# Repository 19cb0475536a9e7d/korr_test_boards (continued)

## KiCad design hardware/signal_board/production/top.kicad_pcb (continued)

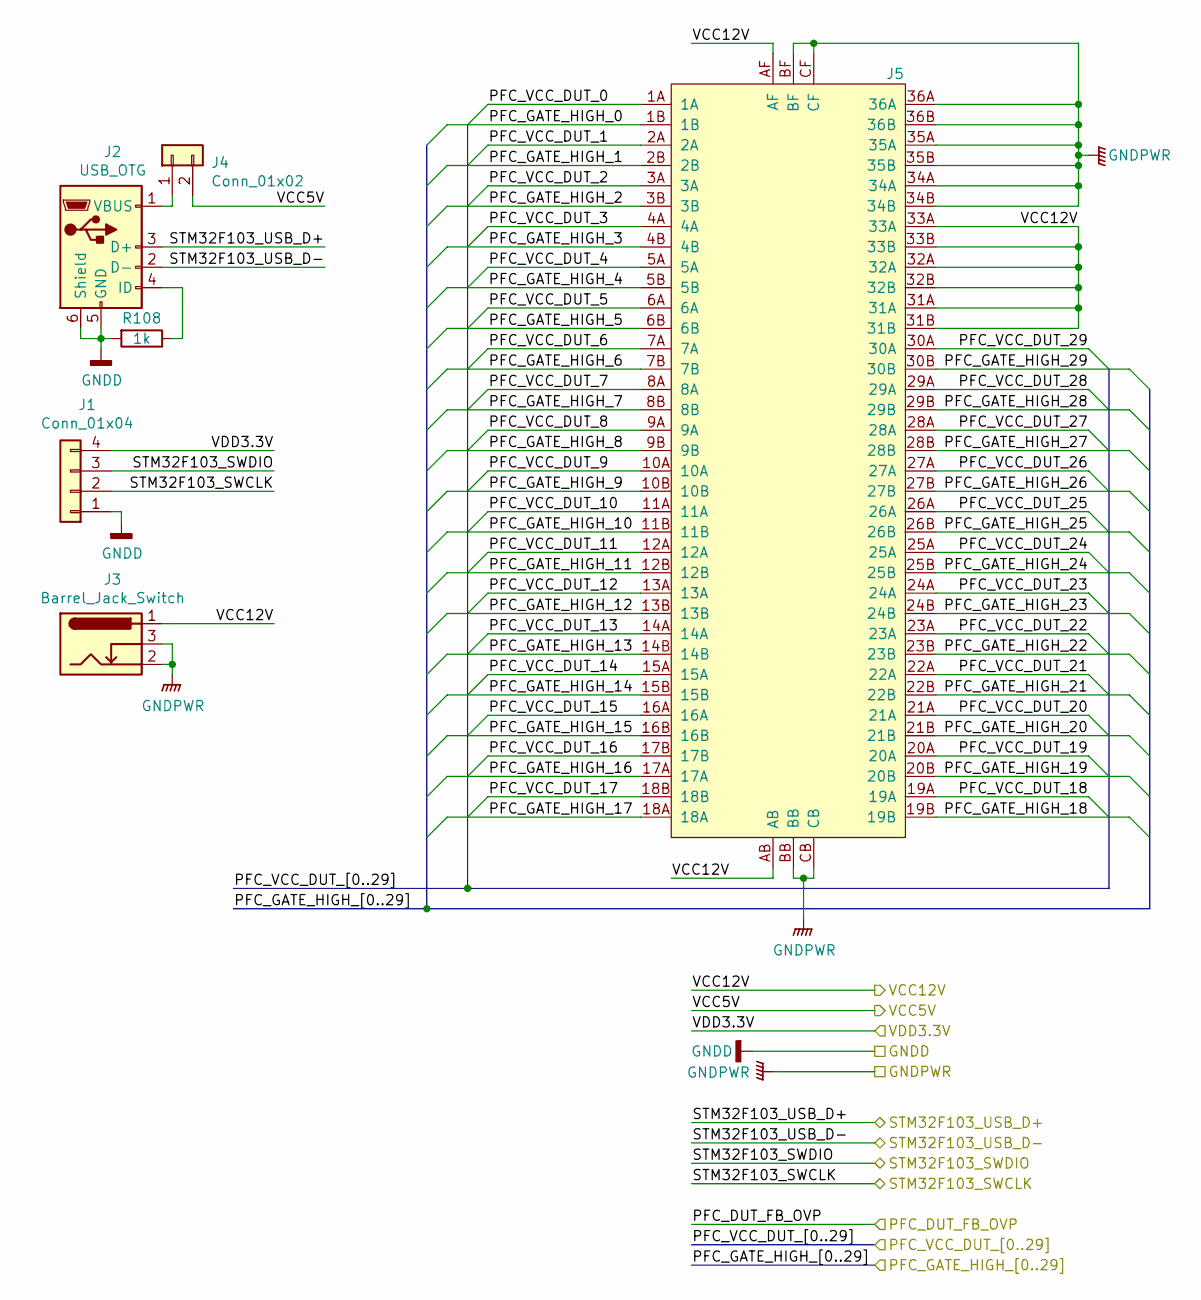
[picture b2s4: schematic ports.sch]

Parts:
J1: Conn_01x04; PinHeader_1x04_P2.54mm_Vertical
J2: USB_OTG; USB_Micro-B_GCT_USB3076-30-A
J3: Barrel_Jack_Switch; BarrelJack_Horizontal
J4: Conn_01x02; PinHeader_1x02_P2.54mm_Vertical
J5: panel_pin; panel_pin_small
R108: 1k; R_0603_1608Metric

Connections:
/PFC_GATE_HIGH_0: J5.1B; also elsewhere on the board
/PFC_GATE_HIGH_1: J5.2B; also elsewhere on the board
/PFC_GATE_HIGH_2: J5.3B; also elsewhere on the board
/PFC_GATE_HIGH_3: J5.4B; also elsewhere on the board
/PFC_GATE_HIGH_4: J5.5B; also elsewhere on the board
/PFC_GATE_HIGH_5: J5.6B; also elsewhere on the board
/PFC_GATE_HIGH_6: J5.7B; also elsewhere on the board
/PFC_GATE_HIGH_7: J5.8B; also elsewhere on the board
/PFC_GATE_HIGH_8: J5.9B; also elsewhere on the board
/PFC_GATE_HIGH_9: J5.10B; also elsewhere on the board
/PFC_GATE_HIGH_10: J5.11B; also elsewhere on the board
/PFC_GATE_HIGH_11: J5.12B; also elsewhere on the board
/PFC_GATE_HIGH_12: J5.13B; also elsewhere on the board
/PFC_GATE_HIGH_13: J5.14B; also elsewhere on the board
/PFC_GATE_HIGH_14: J5.15B; also elsewhere on the board
/PFC_GATE_HIGH_15: J5.16B; also elsewhere on the board
/PFC_GATE_HIGH_16: J5.17A; also elsewhere on the board
/PFC_GATE_HIGH_17: J5.18A; also elsewhere on the board
/PFC_GATE_HIGH_18: J5.19B; also elsewhere on the board
/PFC_GATE_HIGH_19: J5.20B; also elsewhere on the board
/PFC_GATE_HIGH_20: J5.21B; also elsewhere on the board
/PFC_GATE_HIGH_21: J5.22B; also elsewhere on the board
/PFC_GATE_HIGH_22: J5.23B; also elsewhere on the board
/PFC_GATE_HIGH_23: J5.24B; also elsewhere on the board
/PFC_GATE_HIGH_24: J5.25B; also elsewhere on the board
/PFC_GATE_HIGH_25: J5.26B; also elsewhere on the board
/PFC_GATE_HIGH_26: J5.27B; also elsewhere on the board
/PFC_GATE_HIGH_27: J5.28B; also elsewhere on the board
/PFC_GATE_HIGH_28: J5.29B; also elsewhere on the board
/PFC_GATE_HIGH_29: J5.30B; also elsewhere on the board
/PFC_VCC_DUT_0: J5.1A; also elsewhere on the board
/PFC_VCC_DUT_1: J5.2A; also elsewhere on the board
/PFC_VCC_DUT_2: J5.3A; also elsewhere on the board
/PFC_VCC_DUT_3: J5.4A; also elsewhere on the board
/PFC_VCC_DUT_4: J5.5A; also elsewhere on the board
/PFC_VCC_DUT_5: J5.6A; also elsewhere on the board
/PFC_VCC_DUT_6: J5.7A; also elsewhere on the board
/PFC_VCC_DUT_7: J5.8A; also elsewhere on the board
/PFC_VCC_DUT_8: J5.9A; also elsewhere on the board
/PFC_VCC_DUT_9: J5.10A; also elsewhere on the board
/PFC_VCC_DUT_10: J5.11A; also elsewhere on the board
/PFC_VCC_DUT_11: J5.12A; also elsewhere on the board
/PFC_VCC_DUT_12: J5.13A; also elsewhere on the board
/PFC_VCC_DUT_13: J5.14A; also elsewhere on the board
/PFC_VCC_DUT_14: J5.15A; also elsewhere on the board
/PFC_VCC_DUT_15: J5.16A; also elsewhere on the board
/PFC_VCC_DUT_16: J5.17B; also elsewhere on the board
/PFC_VCC_DUT_17: J5.18B; also elsewhere on the board
/PFC_VCC_DUT_18: J5.19A; also elsewhere on the board
/PFC_VCC_DUT_19: J5.20A; also elsewhere on the board
/PFC_VCC_DUT_20: J5.21A; also elsewhere on the board
/PFC_VCC_DUT_21: J5.22A; also elsewhere on the board
/PFC_VCC_DUT_22: J5.23A; also elsewhere on the board
/PFC_VCC_DUT_23: J5.24A; also elsewhere on the board
/PFC_VCC_DUT_24: J5.25A; also elsewhere on the board
/PFC_VCC_DUT_25: J5.26A; also elsewhere on the board
/PFC_VCC_DUT_26: J5.27A; also elsewhere on the board
/PFC_VCC_DUT_27: J5.28A; also elsewhere on the board
/PFC_VCC_DUT_28: J5.29A; also elsewhere on the board
/PFC_VCC_DUT_29: J5.30A; also elsewhere on the board
/STM32F103_SWCLK: J1.2; also elsewhere on the board
/STM32F103_SWDIO: J1.3; also elsewhere on the board
/STM32F103_USB_D+: J2.3 (D+); also elsewhere on the board
/STM32F103_USB_D-: J2.2 (D-); also elsewhere on the board
/VCC5V: J4.2; also elsewhere on the board
/VCC12V: J3.1, J5.31A, J5.31B, J5.32A, J5.32B, J5.33A, J5.33B, J5.AB, J5.AF; also elsewhere on the board
/VDD3.3V: J1.4; also elsewhere on the board
GNDA: J1.1, J2.5 (GND), J2.6 (Shield), J3.2, J3.3, J5.34A, J5.34B, J5.35A, J5.35B, J5.36A, J5.36B, J5.BB, J5.BF, J5.CB, J5.CF, R108.2; also elsewhere on the board
unnamed: J2.1 (VBUS), J4.1
unnamed: J2.4 (ID), R108.1

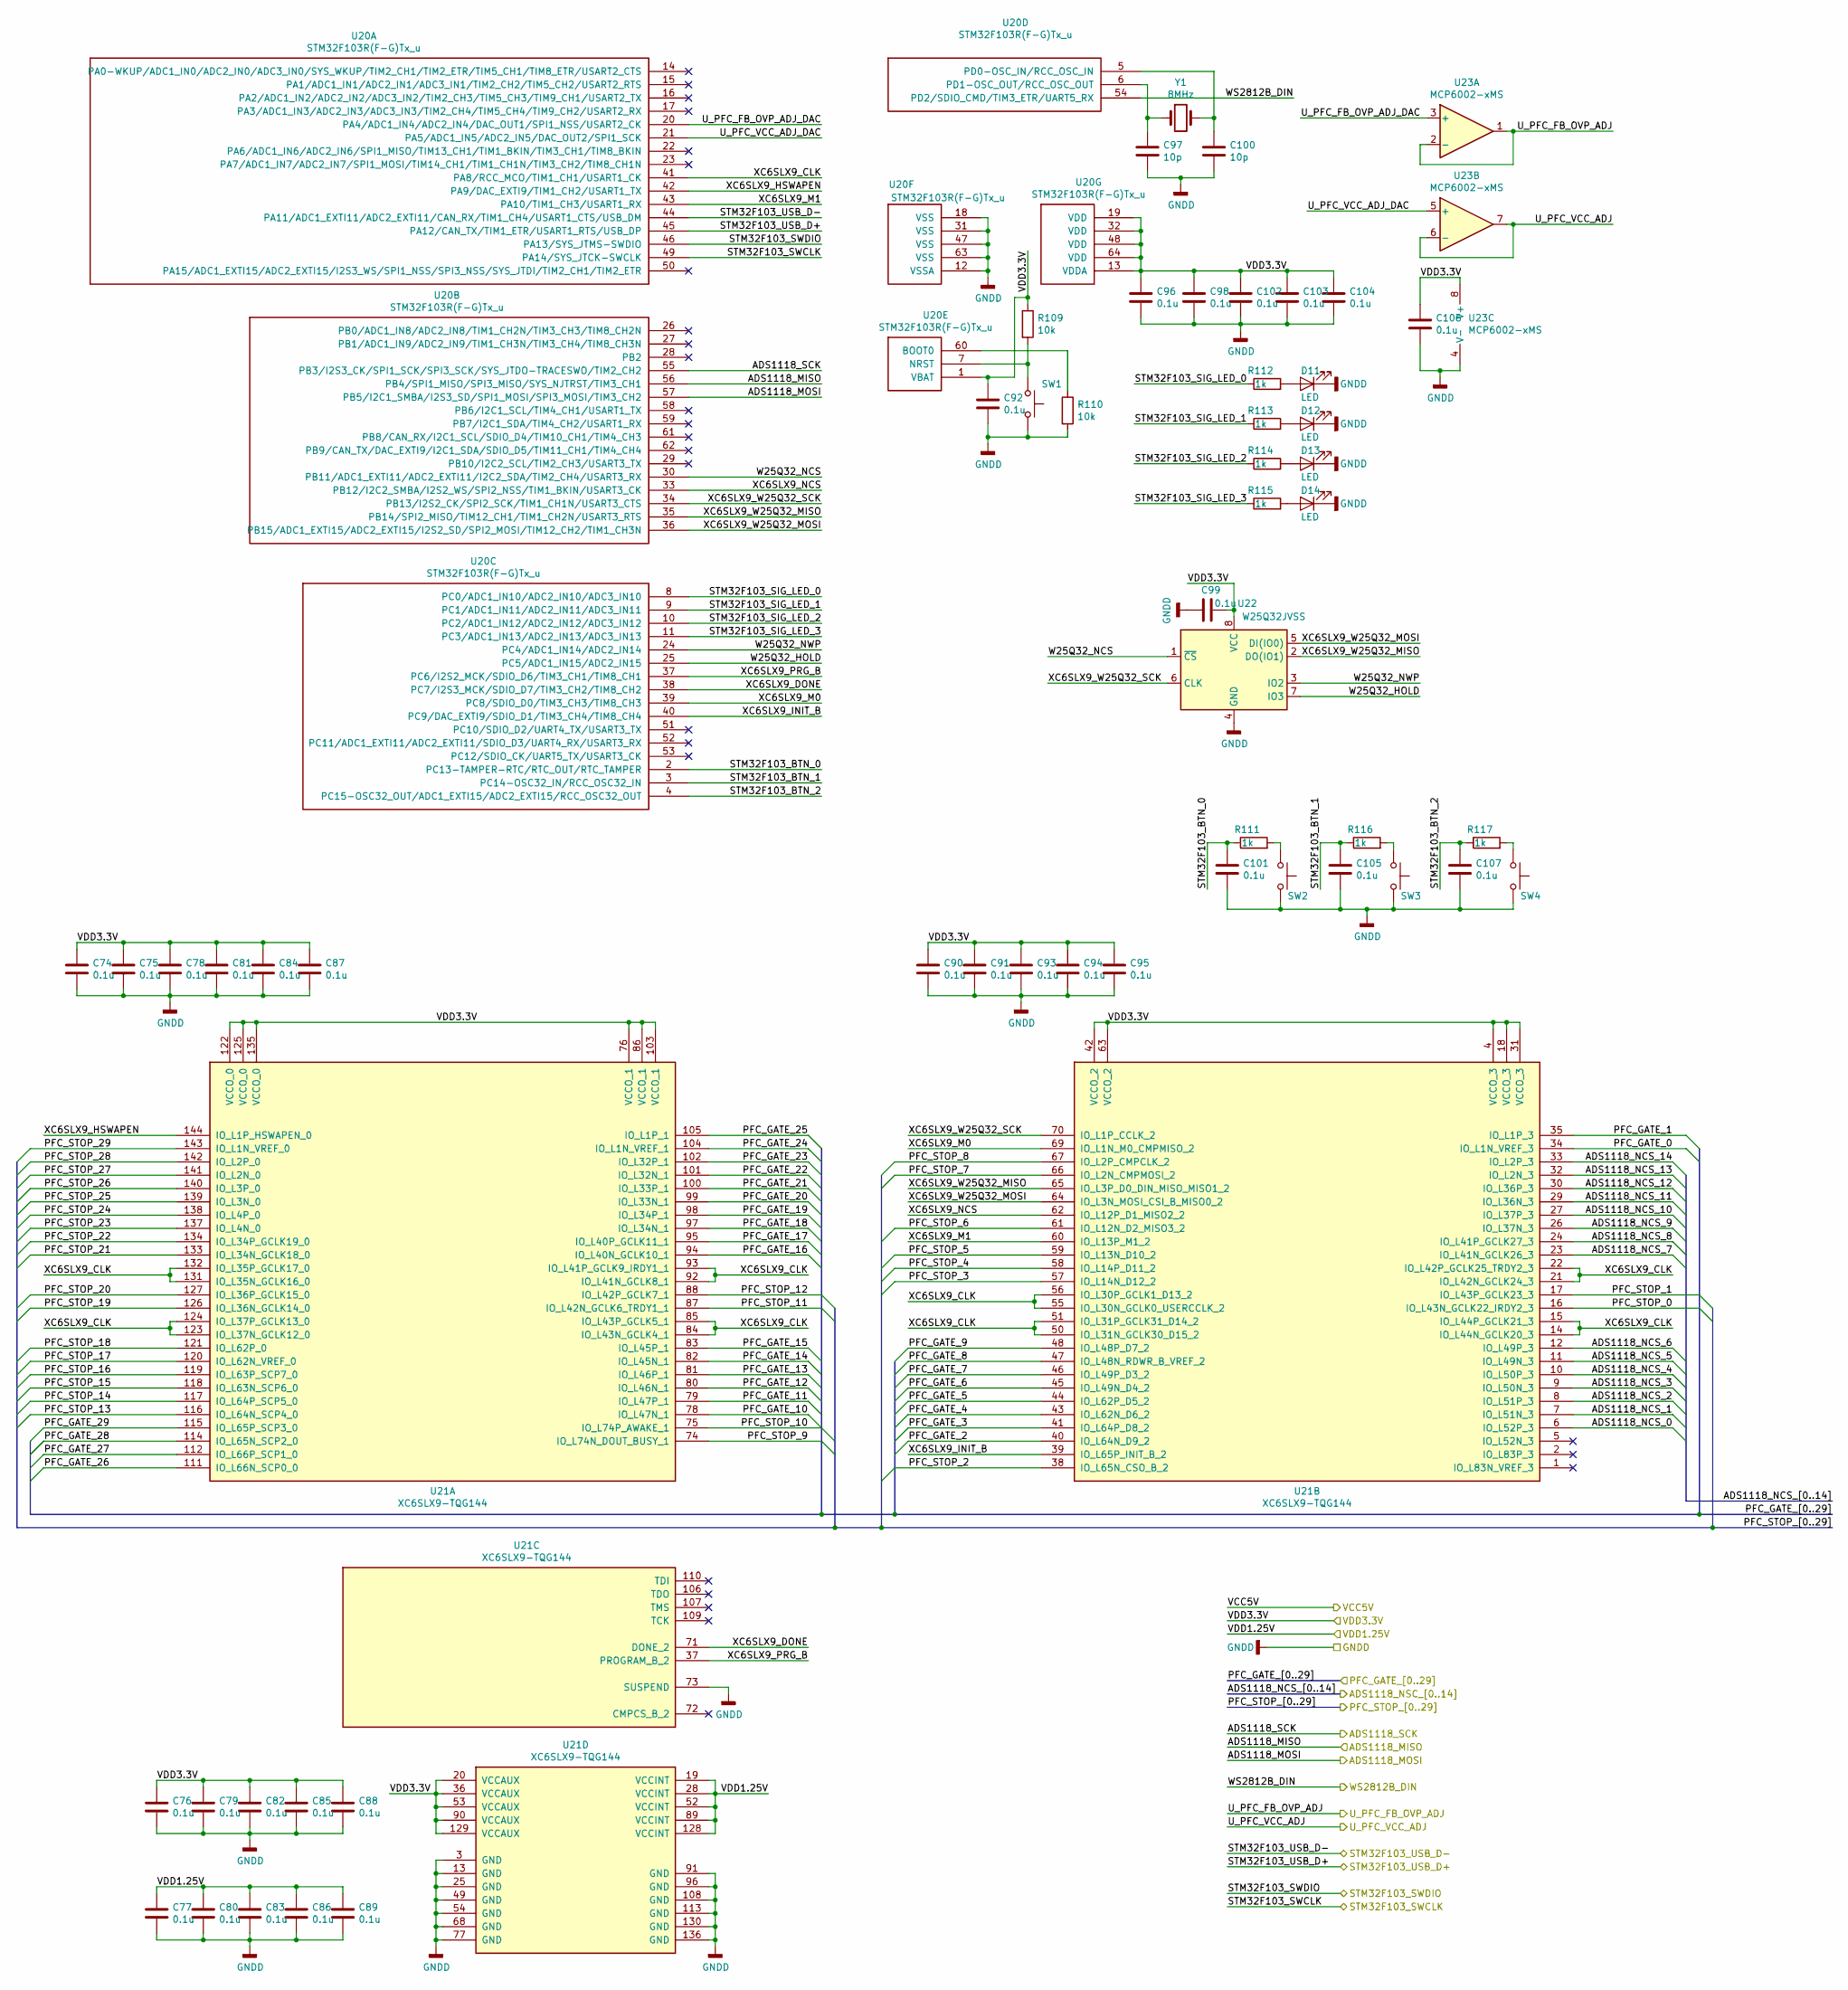
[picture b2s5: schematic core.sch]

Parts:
C74, C75, C76, C77, C78, C79, C80, C81, C82, C83, C84, C85, C86, C87, C88, C89, C90, C91, C92, C93, C94, C95, C96, C98, C99, C101, C102, C103, C104, C105, C106, C107: 0.1u; C_0603_1608Metric
C97, C100: 10p; C_0603_1608Metric
D11, D12, D13, D14: LED; LED_0603_1608Metric
R109, R110: 10k; R_0603_1608Metric
R111, R112, R113, R114, R115, R116, R117: 1k; R_0603_1608Metric
SW1, SW2, SW3, SW4: SW_Push; SW_SPST_B3S-1000
U20: STM32F103R(F-G)Tx_u; LQFP-64_10x10mm_P0.5mm
U21: XC6SLX9-TQG144; TQFP-144_20x20mm_P0.5mm
U22: W25Q32JVSS; SOIC-8_5.23x5.23mm_P1.27mm
U23: MCP6002-xMS; SOIC-8_3.9x4.9mm_P1.27mm
Y1: 8MHz; Crystal_SMD_7050-2Pin_7.0x5.0mm

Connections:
/ADS1118_MISO: U20.56 (PB4/SPI1_MISO/SPI3_MISO/SYS_NJTRST/TIM3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); also elsewhere on the board
/ADS1118_MOSI: U20.57 (PB5/I2C1_SMBA/I2S3_SD/SPI1_MOSI/SPI3_MO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); also elsewhere on the board
/ADS1118_NCS_0: U21.6 (IO_L52P_3); also elsewhere on the board
/ADS1118_NCS_1: U21.7 (IO_L51N_3); also elsewhere on the board
/ADS1118_NCS_2: U21.8 (IO_L51P_3); also elsewhere on the board
/ADS1118_NCS_3: U21.9 (IO_L50N_3); also elsewhere on the board
/ADS1118_NCS_4: U21.10 (IO_L50P_3); also elsewhere on the board
/ADS1118_NCS_5: U21.11 (IO_L49N_3); also elsewhere on the board
/ADS1118_NCS_6: U21.12 (IO_L49P_3); also elsewhere on the board
/ADS1118_NCS_7: U21.23 (IO_L41N_GCLK26_3); also elsewhere on the board
/ADS1118_NCS_8: U21.24 (IO_L41P_GCLK27_3); also elsewhere on the board
/ADS1118_NCS_9: U21.26 (IO_L37N_3); also elsewhere on the board
/ADS1118_NCS_10: U21.27 (IO_L37P_3); also elsewhere on the board
/ADS1118_NCS_11: U21.29 (IO_L36N_3); also elsewhere on the board
/ADS1118_NCS_12: U21.30 (IO_L36P_3); also elsewhere on the board
/ADS1118_NCS_13: U21.32 (IO_L2N_3); also elsewhere on the board
/ADS1118_NCS_14: U21.33 (IO_L2P_3); also elsewhere on the board
/ADS1118_SCK: U20.55 (PB3/I2S3_CK/SPI1_SCK/SPI3_SCK/SYS_JTDO-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); also elsewhere on the board
/CoreSheet/STM32F103_BTN_0: C101.1, R111.1, U20.2 (PC13-TAMPER-RTC/RTC_OUT/RTC_TAMPER)
/CoreSheet/STM32F103_BTN_1: C105.1, R116.1, U20.3 (PC14-OSC32_IN/RCC_OSC32_IN)
/CoreSheet/STM32F103_BTN_2: C107.1, R117.1, U20.4 (PC15-OSC32_OUT/ADC1_EXTI15/ADC2_EXTI15/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)
/CoreSheet/STM32F103_SIG_LED_0: R112.1, U20.8 (PC0/ADC1_IN10/ADC2_IN10/ADC3_IN10)
/CoreSheet/STM32F103_SIG_LED_1: R113.1, U20.9 (PC1/ADC1_IN11/ADC2_IN11/ADC3_IN11)
/CoreSheet/STM32F103_SIG_LED_2: R114.1, U20.10 (PC2/ADC1_IN12/ADC2_IN12/ADC3_IN12)
/CoreSheet/STM32F103_SIG_LED_3: R115.1, U20.11 (PC3/ADC1_IN13/ADC2_IN13/ADC3_IN13)
/CoreSheet/U_PFC_FB_OVP_ADJ_DAC: U20.20 (PA4/ADC1_IN4/ADC2_IN4/DAC_OUT1/SPI1_NSS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), U23.3 (+)
/CoreSheet/U_PFC_VCC_ADJ_DAC: U20.21 (PA5/ADC1_IN5/ADC2_IN5/DAC_OUT2/SPI1_SCK), U23.5 (+)
/CoreSheet/W25Q32_HOLD: U20.25 (PC5/ADC1_IN15/ADC2_IN15), U22.7 (IO3)
/CoreSheet/W25Q32_NCS: U20.30 (PB11/ADC1_EXTI11/ADC2_EXTI11/I2C2_SDA/T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), U22.1 (~CS)
/CoreSheet/W25Q32_NWP: U20.24 (PC4/ADC1_IN14/ADC2_IN14), U22.3 (IO2)
/CoreSheet/XC6SLX9_CLK: U20.41 (PA8/RCC_MCO/TIM1_CH1/USART1_CK), U21.14 (IO_L44N_GCLK20_3), U21.15 (IO_L44P_GCLK21_3), U21.21 (IO_L42N_GCLK24_3), U21.22 (IO_L42P_GCLK25_TRDY2_3), U21.50 (IO_L31N_GCLK30_D15_2), U21.51 (IO_L31P_GCLK31_D14_2), U21.55 (IO_L30N_GCLK0_USERCCLK_2), U21.56 (IO_L30P_GCLK1_D13_2), U21.84 (IO_L43N_GCLK4_1), U21.85 (IO_L43P_GCLK5_1), U21.92 (IO_L41N_GCLK8_1), U21.93 (IO_L41P_GCLK9_IRDY1_1), U21.123 (IO_L37N_GCLK12_0), U21.124 (IO_L37P_GCLK13_0), U21.131 (IO_L35N_GCLK16_0), U21.132 (IO_L35P_GCLK17_0)
/CoreSheet/XC6SLX9_DONE: U20.38 (PC7/I2S3_MCK/SDIO_D7/TIM3_CH2/TIM8_CH2), U21.71 (DONE_2)
/CoreSheet/XC6SLX9_HSWAPEN: U20.42 (PA9/DAC_EXTI9/TIM1_CH2/USART1_TX), U21.144 (IO_L1P_HSWAPEN_0)
/CoreSheet/XC6SLX9_INIT_B: U20.40 (PC9/DAC_EXTI9/SDIO_D1/TIM3_CH4/TIM8_CH4), U21.39 (IO_L65P_INIT_B_2)
/CoreSheet/XC6SLX9_M0: U20.39 (PC8/SDIO_D0/TIM3_CH3/TIM8_CH3), U21.69 (IO_L1N_M0_CMPMISO_2)
/CoreSheet/XC6SLX9_M1: U20.43 (PA10/TIM1_CH3/USART1_RX), U21.60 (IO_L13P_M1_2)
/CoreSheet/XC6SLX9_NCS: U20.33 (PB12/I2C2_SMBA/I2S2_WS/SPI2_NSS/TIM1_BK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), U21.62 (IO_L12P_D1_MISO2_2)
/CoreSheet/XC6SLX9_PRG_B: U20.37 (PC6/I2S2_MCK/SDIO_D6/TIM3_CH1/TIM8_CH1), U21.37 (PROGRAM_B_2)
/CoreSheet/XC6SLX9_W25Q32_MISO: U20.35 (PB14/SPI2_MISO/TIM12_CH1/TIM1_CH2N/USAR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), U21.65 (IO_L3P_D0_DIN_MISO_MISO1_2), U22.2 (DO(IO1))
/CoreSheet/XC6SLX9_W25Q32_MOSI: U20.36 (PB15/ADC1_EXTI15/ADC2_EXTI15/I2S2_SD/SP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), U21.64 (IO_L3N_MOSI_CSI_B_MISO0_2), U22.5 (DI(IO0))
/CoreSheet/XC6SLX9_W25Q32_SCK: U20.34 (PB13/I2S2_CK/SPI2_SCK/TIM1_CH1N/USART3_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), U21.70 (IO_L1P_CCLK_2), U22.6 (CLK)
/PFC_GATE_LOW_0: U21.34 (IO_L1N_VREF_3); also elsewhere on the board
/PFC_GATE_LOW_1: U21.35 (IO_L1P_3); also elsewhere on the board
/PFC_GATE_LOW_2: U21.40 (IO_L64N_D9_2); also elsewhere on the board
/PFC_GATE_LOW_3: U21.41 (IO_L64P_D8_2); also elsewhere on the board
/PFC_GATE_LOW_4: U21.43 (IO_L62N_D6_2); also elsewhere on the board
/PFC_GATE_LOW_5: U21.44 (IO_L62P_D5_2); also elsewhere on the board
/PFC_GATE_LOW_6: U21.45 (IO_L49N_D4_2); also elsewhere on the board
/PFC_GATE_LOW_7: U21.46 (IO_L49P_D3_2); also elsewhere on the board
/PFC_GATE_LOW_8: U21.47 (IO_L48N_RDWR_B_VREF_2); also elsewhere on the board
/PFC_GATE_LOW_9: U21.48 (IO_L48P_D7_2); also elsewhere on the board
/PFC_GATE_LOW_10: U21.78 (IO_L47N_1); also elsewhere on the board
/PFC_GATE_LOW_11: U21.79 (IO_L47P_1); also elsewhere on the board
/PFC_GATE_LOW_12: U21.80 (IO_L46N_1); also elsewhere on the board
/PFC_GATE_LOW_13: U21.81 (IO_L46P_1); also elsewhere on the board
/PFC_GATE_LOW_14: U21.82 (IO_L45N_1); also elsewhere on the board
/PFC_GATE_LOW_15: U21.83 (IO_L45P_1); also elsewhere on the board
/PFC_GATE_LOW_16: U21.94 (IO_L40N_GCLK10_1); also elsewhere on the board
/PFC_GATE_LOW_17: U21.95 (IO_L40P_GCLK11_1); also elsewhere on the board
/PFC_GATE_LOW_18: U21.97 (IO_L34N_1); also elsewhere on the board
/PFC_GATE_LOW_19: U21.98 (IO_L34P_1); also elsewhere on the board
/PFC_GATE_LOW_20: U21.99 (IO_L33N_1); also elsewhere on the board
/PFC_GATE_LOW_21: U21.100 (IO_L33P_1); also elsewhere on the board
/PFC_GATE_LOW_22: U21.101 (IO_L32N_1); also elsewhere on the board
/PFC_GATE_LOW_23: U21.102 (IO_L32P_1); also elsewhere on the board
/PFC_GATE_LOW_24: U21.104 (IO_L1N_VREF_1); also elsewhere on the board
/PFC_GATE_LOW_25: U21.105 (IO_L1P_1); also elsewhere on the board
/PFC_GATE_LOW_26: U21.111 (IO_L66N_SCP0_0); also elsewhere on the board
/PFC_GATE_LOW_27: U21.112 (IO_L66P_SCP1_0); also elsewhere on the board
/PFC_GATE_LOW_28: U21.114 (IO_L65N_SCP2_0); also elsewhere on the board
/PFC_GATE_LOW_29: U21.115 (IO_L65P_SCP3_0); also elsewhere on the board
/PFC_STOP_0: U21.16 (IO_L43N_GCLK22_IRDY2_3); also elsewhere on the board
/PFC_STOP_1: U21.17 (IO_L43P_GCLK23_3); also elsewhere on the board
/PFC_STOP_2: U21.38 (IO_L65N_CSO_B_2); also elsewhere on the board
/PFC_STOP_3: U21.57 (IO_L14N_D12_2); also elsewhere on the board
/PFC_STOP_4: U21.58 (IO_L14P_D11_2); also elsewhere on the board
/PFC_STOP_5: U21.59 (IO_L13N_D10_2); also elsewhere on the board
/PFC_STOP_6: U21.61 (IO_L12N_D2_MISO3_2); also elsewhere on the board
/PFC_STOP_7: U21.66 (IO_L2N_CMPMOSI_2); also elsewhere on the board
/PFC_STOP_8: U21.67 (IO_L2P_CMPCLK_2); also elsewhere on the board
/PFC_STOP_9: U21.74 (IO_L74N_DOUT_BUSY_1); also elsewhere on the board
/PFC_STOP_10: U21.75 (IO_L74P_AWAKE_1); also elsewhere on the board
/PFC_STOP_11: U21.87 (IO_L42N_GCLK6_TRDY1_1); also elsewhere on the board
/PFC_STOP_12: U21.88 (IO_L42P_GCLK7_1); also elsewhere on the board
/PFC_STOP_13: U21.116 (IO_L64N_SCP4_0); also elsewhere on the board
/PFC_STOP_14: U21.117 (IO_L64P_SCP5_0); also elsewhere on the board
/PFC_STOP_15: U21.118 (IO_L63N_SCP6_0); also elsewhere on the board
/PFC_STOP_16: U21.119 (IO_L63P_SCP7_0); also elsewhere on the board
/PFC_STOP_17: U21.120 (IO_L62N_VREF_0); also elsewhere on the board
/PFC_STOP_18: U21.121 (IO_L62P_0); also elsewhere on the board
/PFC_STOP_19: U21.126 (IO_L36N_GCLK14_0); also elsewhere on the board
/PFC_STOP_20: U21.127 (IO_L36P_GCLK15_0); also elsewhere on the board
/PFC_STOP_21: U21.133 (IO_L34N_GCLK18_0); also elsewhere on the board
/PFC_STOP_22: U21.134 (IO_L34P_GCLK19_0); also elsewhere on the board
/PFC_STOP_23: U21.137 (IO_L4N_0); also elsewhere on the board
/PFC_STOP_24: U21.138 (IO_L4P_0); also elsewhere on the board
/PFC_STOP_25: U21.139 (IO_L3N_0); also elsewhere on the board
/PFC_STOP_26: U21.140 (IO_L3P_0); also elsewhere on the board
/PFC_STOP_27: U21.141 (IO_L2N_0); also elsewhere on the board
/PFC_STOP_28: U21.142 (IO_L2P_0); also elsewhere on the board
/PFC_STOP_29: U21.143 (IO_L1N_VREF_0); also elsewhere on the board
/STM32F103_SWCLK: U20.46 (PA13/SYS_JTMS-SWDIO); also elsewhere on the board
/STM32F103_SWDIO: U20.49 (PA14/SYS_JTCK-SWCLK); also elsewhere on the board
/STM32F103_USB_D+: U20.45 (PA12/CAN_TX/TIM1_ETR/USART1_RTS/USB_DP); also elsewhere on the board
/STM32F103_USB_D-: U20.44 (PA11/ADC1_EXTI11/ADC2_EXTI11/CAN_RX/TIM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); also elsewhere on the board
/U_PFC_FB_OVP_ADJ: U23.1, U23.2 (-); also elsewhere on the board
/U_PFC_VCC_ADJ: U23.6 (-), U23.7; also elsewhere on the board
/VDD1.25V: C77.1, C80.1, C83.1, C86.1, C89.1, U21.19 (VCCINT), U21.28 (VCCINT), U21.52 (VCCINT), U21.89 (VCCINT), U21.128 (VCCINT); also elsewhere on the board
/VDD3.3V: C74.1, C75.1, C76.1, C78.1, C79.1, C81.1, C82.1, C84.1, C85.1, C87.1, C88.1, C90.1, C91.1, C92.1, C93.1, C94.1, C95.1, C96.1, C98.1, C99.1, C102.1, C103.1, C104.1, C106.1, R109.1, U20.1 (VBAT), U20.13 (VDDA), U20.19 (VDD), U20.32 (VDD), U20.48 (VDD), U20.64 (VDD), U21.4 (VCCO_3), U21.18 (VCCO_3), U21.20 (VCCAUX), U21.31 (VCCO_3), U21.36 (VCCAUX), U21.42 (VCCO_2), U21.53 (VCCAUX), U21.63 (VCCO_2), U21.76 (VCCO_1), U21.86 (VCCO_1), U21.90 (VCCAUX), U21.103 (VCCO_1), U21.122 (VCCO_0), U21.125 (VCCO_0), U21.129 (VCCAUX), U21.135 (VCCO_0), U22.8 (VCC), U23.8 (V+); also elsewhere on the board
/WS2812B_DIN: U20.54 (PD2/SDIO_CMD/TIM3_ETR/UART5_RX); also elsewhere on the board
GNDA: C74.2, C75.2, C76.2, C77.2, C78.2, C79.2, C80.2, C81.2, C82.2, C83.2, C84.2, C85.2, C86.2, C87.2, C88.2, C89.2, C90.2, C91.2, C92.2, C93.2, C94.2, C95.2, C96.2, C97.2, C98.2, C99.2, C100.2, C101.2, C102.2, C103.2, C104.2, C105.2, C106.2, C107.2, D11.1 (K), D12.1 (K), D13.1 (K), D14.1 (K), R110.2, SW1.2, SW2.2, SW3.2, SW4.2, U20.12 (VSSA), U20.18 (VSS), U20.31 (VSS), U20.47 (VSS), U20.63 (VSS), U21.3 (GND), U21.13 (GND), U21.25 (GND), U21.49 (GND), U21.54 (GND), U21.68 (GND), U21.73 (SUSPEND), U21.77 (GND), U21.91 (GND), U21.96 (GND), U21.108 (GND), U21.113 (GND), U21.130 (GND), U21.136 (GND), U22.4 (GND), U23.4 (V-); also elsewhere on the board
unnamed: C97.1, U20.6 (PD1-OSC_OUT/RCC_OSC_OUT), Y1.1
unnamed: C100.1, U20.5 (PD0-OSC_IN/RCC_OSC_IN), Y1.2
unnamed: D11.2 (A), R112.2
unnamed: D12.2 (A), R113.2
unnamed: D13.2 (A), R114.2
unnamed: D14.2 (A), R115.2
unnamed: R109.2, SW1.1, U20.7 (NRST)
unnamed: R110.1, U20.60 (BOOT0)
unnamed: R111.2, SW2.1
unnamed: R116.2, SW3.1
unnamed: R117.2, SW4.1
